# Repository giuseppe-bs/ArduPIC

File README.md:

# ArduPIC

A prototyping board based on the PIC18F4520 microcontroller. Featuring self power as well as USB power. This project was submitted as an evaluative assignment in the electronics co-design class (PBLE) at the Federal University of Itajubá (UNIFEI)

## 3D View

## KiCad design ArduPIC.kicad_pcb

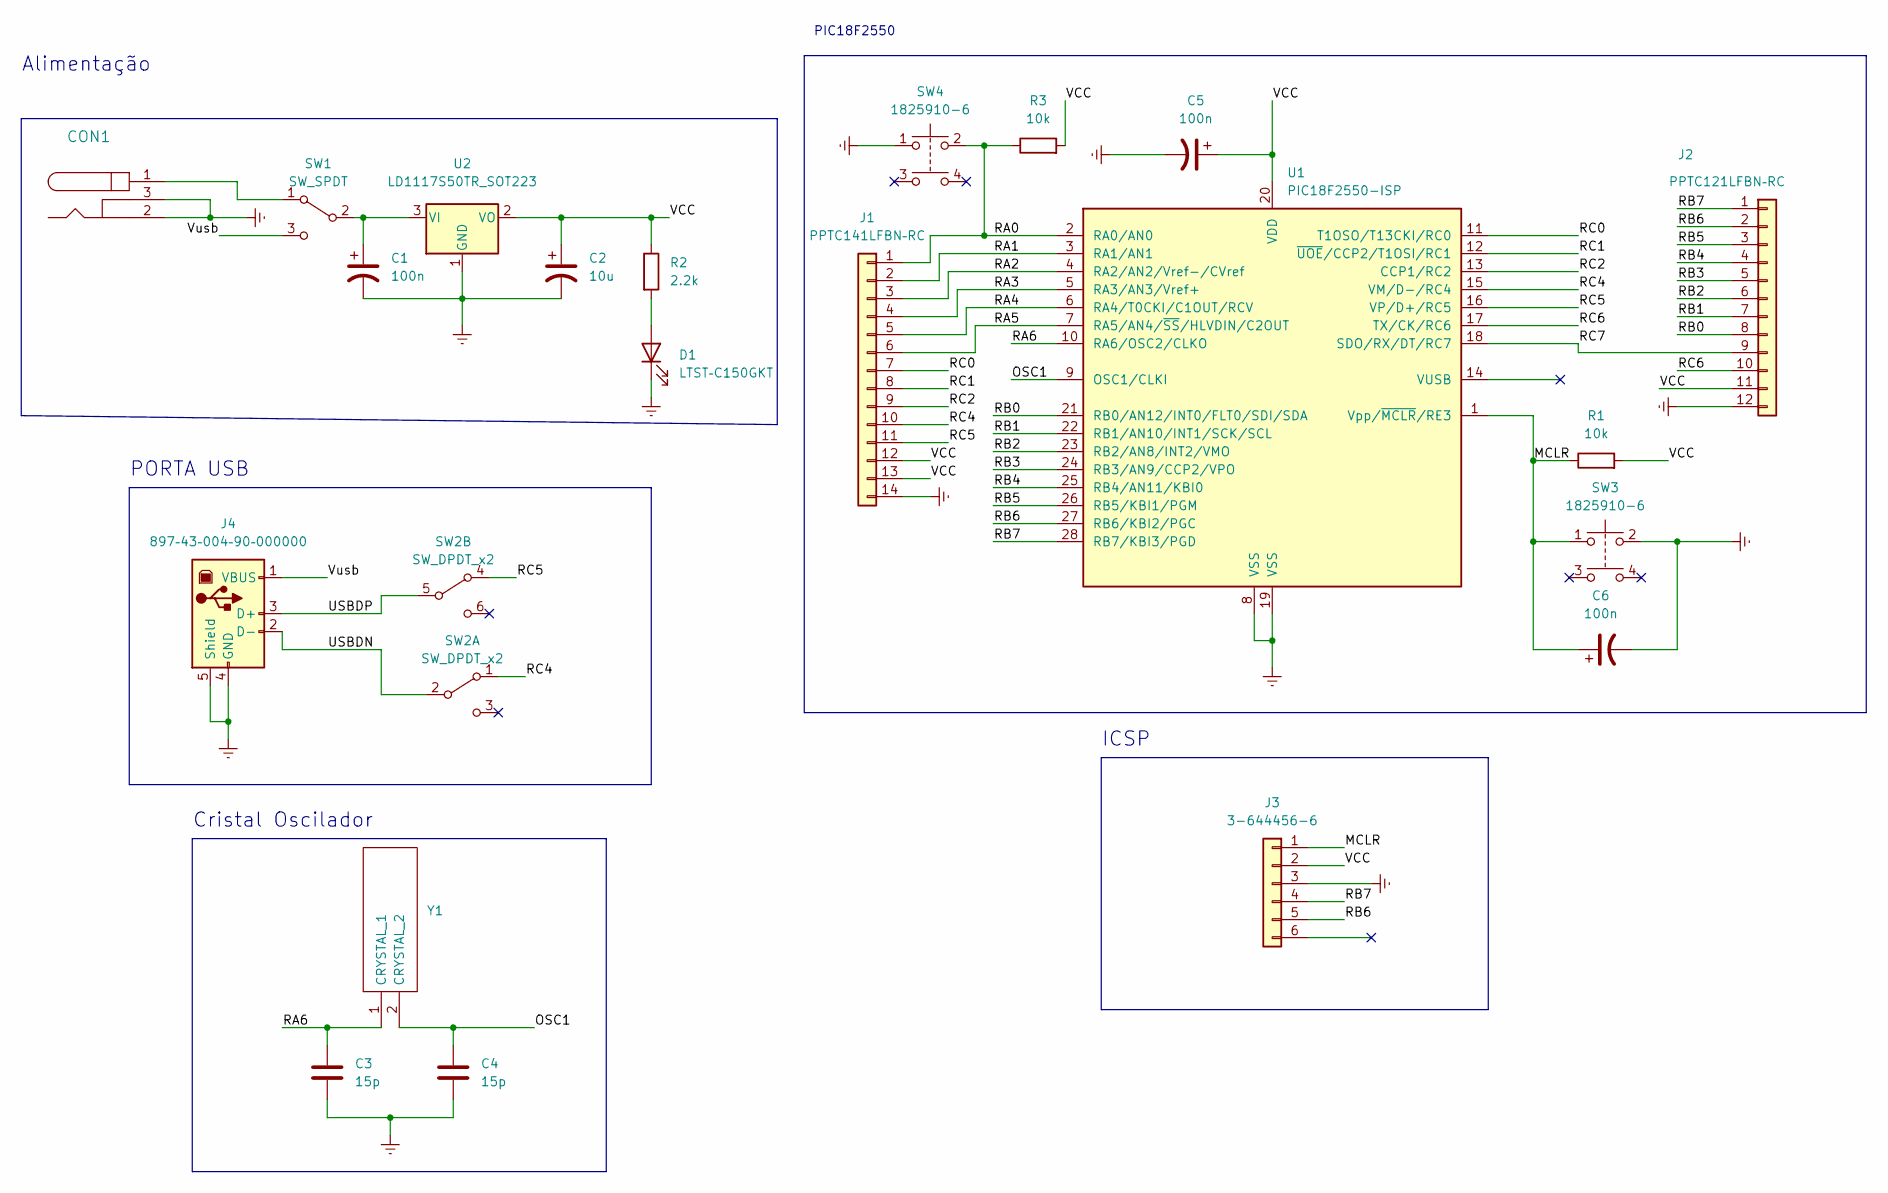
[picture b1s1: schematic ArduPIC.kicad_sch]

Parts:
C1: 100n; C_0805_2012Metric_Pad1.18x1.45mm_HandSolder
C2: 10u; C_1206_3216Metric_Pad1.33x1.80mm_HandSolder
C3, C4: 15p; C_0805_2012Metric_Pad1.18x1.45mm_HandSolder
C5, C6: 100n; C_1206_3216Metric_Pad1.33x1.80mm_HandSolder
CON1: (no value)
D1: LTST–C150GKT; LED_1206_3216Metric_Pad1.42x1.75mm_HandSolder
J1: PPTC141LFBN–RC; PinSocket_1x14_P2.54mm_Vertical
J2: PPTC121LFBN–RC; PinSocket_1x12_P2.54mm_Vertical
J3: 3-644456-6; PinHeader_1x06_P2.54mm_Vertical
J4: 897–43–004–90–000000; USB_B_OST_USB-B1HSxx_Horizontal
R1, R3: 10k; R_0805_2012Metric_Pad1.20x1.40mm_HandSolder
R2: 2.2k; LED_0805_2012Metric_Pad1.15x1.40mm_HandSolder
SW1: SW_SPDT; SW_SPDT_CK-JS102011SAQN
SW2: SW_DPDT_x2; SW_DPDT_CK_JS202011JCQN
SW3, SW4: 1825910-6; SW_PUSH_6mm
U1: PIC18F2550-ISP; DIP-28_W7.62mm
U2: LD1117S50TR_SOT223; SOT-223-3_TabPin2
Y1: ATS20A; Manufacturer_Part_Number ATS20A; Mouser Part Number 774-ATS20A

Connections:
/MCLR: C6.1, J3.1, R1.1, SW3.1, U1.1 (Vpp/~MCLR/RE3)
/OSC1: C4.1, U1.9 (OSC1/CLKI), Y1.2 (CRYSTAL)
/RA0: J1.1, R3.1, SW4.2, U1.2 (RA0/AN0)
/RA1: J1.2, U1.3 (RA1/AN1)
/RA2: J1.3, U1.4 (RA2/AN2/Vref-/CVref)
/RA3: J1.4, U1.5 (RA3/AN3/Vref+)
/RA4: J1.5, U1.6 (RA4/T0CKI/C1OUT/RCV)
/RA5: J1.6, U1.7 (RA5/AN4/~SS/HLVDIN/C2OUT)
/RA6: C3.1, U1.10 (RA6/OSC2/CLKO), Y1.1 (CRYSTAL)
/RB0: J2.8, U1.21 (RB0/AN12/INT0/FLT0/SDI/SDA)
/RB1: J2.7, U1.22 (RB1/AN10/INT1/SCK/SCL)
/RB2: J2.6, U1.23 (RB2/AN8/INT2/VMO)
/RB3: J2.5, U1.24 (RB3/AN9/CCP2/VPO)
/RB4: J2.4, U1.25 (RB4/AN11/KBI0)
/RB5: J2.3, U1.26 (RB5/KBI1/PGM)
/RB6: J2.2, J3.5, U1.27 (RB6/KBI2/PGC)
/RB7: J2.1, J3.4, U1.28 (RB7/KBI3/PGD)
/RC0: J1.7, U1.11 (T1OSO/T13CKI/RC0)
/RC1: J1.8, U1.12 (~UOE/CCP2/T1OSI/RC1)
/RC2: J1.9, U1.13 (CCP1/RC2)
/RC4: J1.10, SW2.1 (A), U1.15 (VM/D-/RC4)
/RC5: J1.11, SW2.4 (A), U1.16 (VP/D+/RC5)
/RC6: J2.10, U1.17 (TX/CK/RC6)
/RC7: J2.9, U1.18 (SDO/RX/DT/RC7)
/USBDN: J4.2 (D-), SW2.2 (B); also elsewhere on the board
/USBDP: J4.3 (D+), SW2.5 (B); also elsewhere on the board
/VCC: C2.1, C5.1, J1.12, J1.13, J2.11, J3.2, R1.2, R2.1, R3.2, U1.20 (VDD), U2.2 (VO)
/Vusb: J4.1 (VBUS), SW1.3 (C); also elsewhere on the board
Earth: C1.2, C2.2, C3.2, C4.2, C5.2, C6.2, CON1.2, CON1.3, D1.1 (K), J1.14, J2.12, J3.3, J4.4 (GND), J4.5 (Shield), SW3.2, SW4.1, U1.8 (VSS), U1.19 (VSS), U2.1 (GND); also elsewhere on the board
unnamed: C1.1, SW1.2 (B), U2.3 (VI)
unnamed 30: CON1.1, SW1.1 (A); also elsewhere on the board
unnamed: D1.2 (A), R2.2

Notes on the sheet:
PORTA USB
PIC18F2550
Cristal Oscilador
Alimentação
ICSP

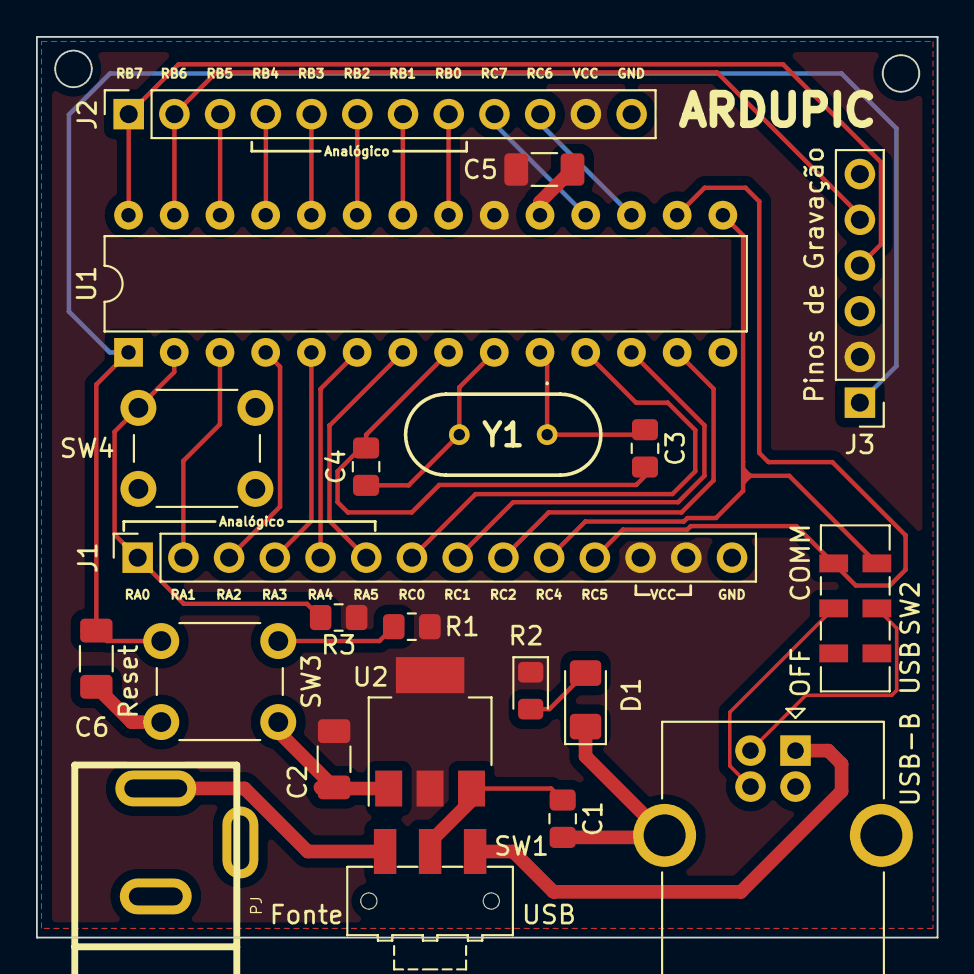
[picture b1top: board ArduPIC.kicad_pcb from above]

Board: 2 copper layers, 50.0 x 50.0 mm, 22 parts (0 on the bottom side), 32 nets.

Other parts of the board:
PJ: PJ-002
USB-B: 897–43–004–90–000000; USB_B_OST_USB-B1HSxx_Horizontal

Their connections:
/USBDN: USB-B.2 (D-); also elsewhere on the board
/USBDP: USB-B.3 (D+); also elsewhere on the board
/Vusb: USB-B.1 (VBUS); also elsewhere on the board
Earth: PJ.2, PJ.3, USB-B.4 (GND), USB-B.5 (Shield); also elsewhere on the board
unnamed 30: PJ.1; also elsewhere on the board

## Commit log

2022-05-18 Ardupic commit
2022-05-18 Models update
